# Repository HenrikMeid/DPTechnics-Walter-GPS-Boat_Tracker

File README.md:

### Lage:

Ein Sportboot wird von mehreren Parteien genutzt. Darüber hinaus ist es mit einer automatischen Lenzpumpe ausgestattet, die bei Regenfall das im Boot anfallende Wasser abpumpt. Um die aktuelle Position des Bootes für alle Beteiligten sichtbar zu machen, gefahrene Routen nachvollziehen zu können und zusätzlich zu erkennen, ob die automatische Pumpe tatsächlich aktiv war, wurde das folgende Projekt umgesetzt.  

# DPTechnics Walter Boat-tracker

Das obenstehende Projekt nutzt die [GNSS](https://de.wikipedia.org/wiki/Globales_Navigationssatellitensystem)- und LTE-Funktionalität des [DPTechnics Walter Dev Boards](https://www.quickspot.io/index.html), um Positions- und Sensordaten eines Sportbootes zu erfassen und an ein serverseitiges Backend zu übertragen. Dieses speichert die empfangenen Daten in einer Datenbank und bereitet sie in einem [Webfrontend](#Walktrough) zur Darstellung auf.
Die nachfolgende Grafik stellt den Ablauf schematisch dar.

Der DPTechnics Walter sendet seine aktuelle Position sowie beliebige weitere Sensorwerte ([GPIO's](https://de.wikipedia.org/wiki/GPIO)) per CoAP oder [HTTPS](https://de.wikipedia.org/wiki/Hypertext_Transfer_Protocol) POST an die DynDNS-Adresse des Servers, der zusätzlich durch einen Reverse Proxy ([NGINX](https://de.wikipedia.org/wiki/Nginx)) abgesichert ist. Über entsprechende Routen werden die Daten mit einem Zeitstempel versehen und in eine SQLite-Datenbank geschrieben.

Zur Verarbeitung und Darstellung der Daten auf einem Webserver kommt serverseitig ein Python-[Flask](https://flask.palletsprojects.com/en/stable/deploying/)-Skript zum Einsatz. Der gesamte Datenaustausch erfolgt aktuell über API-Calls mit dem [Flask-Server](https://flask.palletsprojects.com/en/stable/deploying/). [Gunicorn](https://gunicorn.org/) fungiert dabei als [WSGI-Server](https://de.wikipedia.org/wiki/Web_Server_Gateway_Interface) und übernimmt das Handling mehrerer User-Clients sowie die [WSGI-HTTPS](https://de.wikipedia.org/wiki/Web_Server_Gateway_Interface)-Übersetzung.

Über die Website können Anfragen – beispielsweise zur aktuellen Position des Bootes – an den Server gestellt werden. Dieser liest die entsprechenden Daten aus der Datenbank aus und übergibt sie an das JavaScript der Webseite, welches sie visuell darstellt.

Für ein zweckmäßiges [CD/CI-Setup](https://de.wikipedia.org/wiki/CI/CD) wurde für den privaten Einsatz die [GitHub Container Registry (GHCR)](https://github.blog/news-insights/product-news/introducing-github-container-registry/) gewählt. Diese kann alternativ problemlos durch den offiziellen [Docker Hub](https://www.docker.com/products/docker-hub/) ersetzt werden ([Infos zu Containerization](https://en.wikipedia.org/wiki/Containerization_(computing))). Entsprechende [Crontabs](https://de.wikipedia.org/wiki/Cron) oder [Webhooks](https://de.wikipedia.org/wiki/Webhook) sind derzeit eigenständig zu implementieren.

# Getting started

Notwendige Hardware- und Softwareanpassungen werden in den folgenden Kapiteln erläutert.

## Prerequisits

> [!NOTE]
>
> * Voraussetzung ist eine eigene global erreichbare IP oder [DynDNS-Adresse](https://de.wikipedia.org/wiki/Dynamisches_DNS). Sehr zu empfehlen ist der kostenlose DynDNS-Host [IPv64.de](https://ipv64.net/)
> * Ebenso wird ein bereits installierter Reverse Proxy o. ä. wie [NGINX](https://nginx.org/) für eine einfache [Let's-Encrypt](https://de.wikipedia.org/wiki/Let%E2%80%99s_Encrypt)-[TLS](https://de.wikipedia.org/wiki/Transport_Layer_Security)-Zertifizierung und optionales Loadbalancing benötigt.
> * Zusätzlich wird eine vorhandene Docker- bzw. Docker-Compose-Installation vorausgesetzt. Siehe [Docker Doku](https://docs.docker.com/engine/install/)
> * Für die Programmierung des ESP32 wurde die [Arduino IDE](https://docs.arduino.cc/software/ide/) verwendet. Details zur Verwendung der Development-Toolchain in der [Arduino IDE](https://docs.arduino.cc/software/ide/) befinden sich in der [DPTechnics Walter Doku](https://www.quickspot.io/documentation.html#/developer-toolchains/arduino)

## Hardware

Das folgende Kapitel erläutert die getroffenen hardwareseitigen Maßnahmen und listet die verwendeten Bauteile auf.

### ESP32 GPIOS

Um die 12 V- und 24 V-Spannungen des Bordnetzes als 3.3 V-Logiksignale nutzbar zu machen, wurde die nachstehende Schaltung entworfen und auf einer Lochrasterplatine umgesetzt.

Die Schaltung für das Erkennen der Pumpe auf der linken Seite ist rechts gespiegelt, nachfolgend wird sich auf die linke Seite beschränkt. Die beim Schalten des Verbrauchers GPIO_13 (Pumpe) anliegende Spannung (Vcc_Boradnetz, 12 -24 V) wird über C2 geglättet und durch D1 auf 10 V begrenzt. Die Spannung am Spannungsteiler R2/R3 schaltet anschließend Q1. Die am Pull-up R4 anliegende Spannung von 3.3 V wird dadurch annähernd auf GND gezogen, wodurch die GPIO's 13 und 38 einen Flankenwechsel erkennen (Wake-up, Interrupt etc.). Dabei kann der [Interrupt/Wakeup](https://de.wikipedia.org/wiki/Interrupt) an GPIO_38 über den Jumper JP1 wahlweise dazugeschalten werden, wenn dieser bei einem Flankenwechsel an GPIO_13 aktiv sein soll. Möchte eine analoge Spannung über einen der internen [ADC's](https://de.wikipedia.org/wiki/Analog-Digital-Umsetzer) gemessen werden, kann das PCB um einen niederohmigen [Trimmer](https://de.wikipedia.org/wiki/Trimmer) an GPIO_12 erweitert werden. Um im weiterer Zukunft weitere [GPIO's](https://de.wikipedia.org/wiki/GPIO) nutzbar machen zu können wurden die GPIOs 40, 41, 42, 2, 1 und 7 an Buchsenleisten herausgeführt. Ebenfalls herausgeführt sind die Seriellen GPIOs 44 und 43, werden aber nicht verwendet. Pin 26 / GPIO_0 versorgt die 3.3 V Ebene des [PCB's](https://de.wikipedia.org/wiki/Polychlorierte_Biphenyle) mit 3.3 V, sowie GND die GND Ebene des zweilagigen PCB (Siehe nächste Abbildung).

Die Pull-up-Spannung wird über den internen [DC/DC-Wandler](https://de.wikipedia.org/wiki/Gleichspannungswandler) des [ESP](https://de.wikipedia.org/wiki/ESP32) selbst bereitgestellt (GPIO_0 = LOW), sofern der [ESP](https://de.wikipedia.org/wiki/ESP32) mit 3.3–5 V über USB-C oder Walter Pin 28 versorgt wird. Da die 3.3 V / 250 mA-Spannungsquelle ebenfalls den Sequans LTE/GNSS-[SoC](https://de.wikipedia.org/wiki/System-on-a-Chip) versorgt, ist es notwendig, neben den internen [Pull-ups](https://www.elektronik-kompendium.de/public/schaerer/pullr.htm) zusätzlich einen externen zu verwenden.

Die Bauteile bzw. die Schaltung wurde nach den Bauteilen entworfen, welche bereits in der Werkstatt des Autors vorhanden waren. Es mag durchaus bessere Lösungen geben. Die [Via's](https://de.wikipedia.org/wiki/Durchkontaktierung) sind einfach da weil der Platz vorhanden ist und warum nicht, kostet nicht mehr, tut niemandem weh und mir macht's Spaß.

DPTechnics Walter / ESP Pinning siehe -> [Doku](https://www.quickspot.io/documentation.html#/hardware/walter). Anschaulich dargestellt ist die fertige Hardware in der oberen Abbildung der Assembly.

> [!IMPORTANT]
> Wichtig ist eine konstante Spannungsquelle für den ESP. Eventuelle Laderegler von Powerbanks o. ä. beenden die Spannungsversorgung im Light- oder Deep-Sleep-Modus des ESP.

### Energieverbrauch

Das System bezieht im getesteten Szenario ca. 11 mAh/Tag (1 h im Zustand/State Fahrt, 23 h deep sleep).  
Im deep sleep Modus, also im Zustand/State Hafen, wird ca. 0,25 mAh/Tag verbraucht.

### Server

Als Server eignet sich grundsätzlich jede lauffähige Hardware. Hier wurde ein Raspberry Pi 5 mit 8 GB RAM verwendet.

### Teileliste

Mindest Anzahl 1x GPIO IN + 1x GPIO Wakeup + 1x ADC-Trimmer GPIO IN:

* Reichelt
  * 1x DPTechnics Walter
  * 4x 1k Widerstand MPR 1,00K
  * 1x 10 V Zener-Diode BZX 85C10 VIS
  * 1x 1x2 Jumper BKL 10120190
  * 1x 1x2 Stiftleiste BKL 10120909
  * 2x 1x14 Buchsenleiste BKL 10120952
  * 1x 1x3 Buchsenleiste BKL 10120717
  * 1x 1x5 Buchsenleiste BKL 10120643
  * 1x Schraubklemme CTB0502-2
  * 2x Schraubklemme CTB0102-3
  * 1x Trimmer 10k 64Y-10K
  * 1x PCB oder Lochrasterplatine LR-DS-KIT
  * 1x Gehäuse 3215000,0H
* Amazon

  * 1x [8 Ader 10AWG Kabel](https://www.amazon.de/dp/B0F2J3JX1M?ref=ppx_yo2ov_dt_b_fed_asin_title)
  * 1x [USB-A DC/DC Wandler 12-5 V](https://www.amazon.de/dp/B0D471BSR2?ref=ppx_yo2ov_dt_b_fed_asin_title)
  * 1x [Schraubverbinder](https://www.amazon.de/dp/B0CYLPM7T7?ref=ppx_yo2ov_dt_b_fed_asin_title)
  * 1x [Sicherungshalter](https://www.amazon.de/dp/B00H3CVSXQ?ref=ppx_yo2ov_dt_b_fed_asin_title)
  * 1x [100 mA Sicherung](https://www.amazon.de/BOJACK-sicherungen-Sortiment-transparenten-Kunststoffbox/dp/B07TF68QZC/ref=sr_1_1_sspa?__mk_de_DE=%C3%85M%C3%85%C5%BD%C3%95%C3%91&crid=N28PGBRT44MQ&dib=eyJ2IjoiMSJ9.sPdAgH-rSnJFHYjegg6Dek2Q75fIi0S6McFGhtfZCjzgh_EctIML_GrF6OmgXMo4czIO8cW98SZEgSEyAAEJxmwuqdoz92V_l-mYqf2NKlNrb9KftnxUi-83u6B079BJfZob5SS1ncg14YnqM1RtYm1rnb2NeMVneedfPabSAqy4ZyhohT7ycUOSktVEu5QRGCjuL90_8qmFwU3k02jZVjznu-b97ms8FXkPfLcSCucvuZw9p0O4m7MyqG4ajsIcs_8uYud1AMbCneMqnoGVlf6sbl-t8s_liqoBa6SfKPQ.GSThK7u_IChCK4kmN7Saj6kUuYZNWmGNsO2dPPZifQI&dib_tag=se&keywords=sicherung%2B150%2BmA%2BF&qid=1770633179&sprefix=sicherung%2B150a%2Bf%2Caps%2C123&sr=8-1-spons&aref=S2wg4qFQ5A&sp_csd=d2lkZ2V0TmFtZT1zcF9hdGY&th=1)
* Bereits vorhanden sein sollte:

  * Altes USB-A Kabel zum verbasteln
  * Crimps etc.

## ESP32S3 Code

Damit der ESP32 die Sensorwerte an den Server senden kann, müssen folgende Parameter in der .ino bzw. den Header-Files des ESP-Codes an den entsprechenden Stellen eingetragen werden:

* IP / URL:

```
#define HTTPS_HOST "adresse.home64.de"

```

* Ports:

```
#define HTTPS_PORT 443
```

* GET / POST Endpoints: (wenn andere gewünscht)

```
#define HTTPS_GET_ENDPOINT "/daten"
#define HTTPS_POST_ENDPOINT "/daten"
```

* BasicAuth Zugangsdaten

```
#define HTTP_USER "user"
#define HTTP_PASS "userpasswort"
```

* **Einmalig** TLS CA:
  Dabei wird das [CA-Zertifikat](https://en.wikipedia.org/wiki/Certificate_authority) mit `PROGMEM` im [Flash](https://de.wikipedia.org/wiki/Flash-Speicher) des ESP32 gespeichert.

```
const char ca_cert[] PROGMEM = R"EOF(
-----BEGIN CERTIFICATE-----
/*Hier CA einfuegen*/
-----END CERTIFICATE-----
)EOF";
```

Die `.tlsWriteCredential()` Methode in `setupTLSProfile()` sollte demnach auch nur einmal nach Eintragung des [CA-Zertifikat](https://en.wikipedia.org/wiki/Certificate_authority) ausgeführt werden. Danach darf der Teil gerne auskommentiert werden (siehe Codebeispiel unten). Anschließend wird das [CA-Zertifikat](https://en.wikipedia.org/wiki/Certificate_authority) beim Setup des TLS-Profils aus dem Flash geladen.

```
bool setupTLSProfile(void){
  // Sollte nur bei Aenderung des CA certs und nach Firmwareupgrade aufgerufen werden
  /*if(!modem.tlsWriteCredential(false, 12, ca_cert)) {
    Serial.println("Error: CA cert upload failed");
    return false;
  }*/

  if(modem.tlsConfigProfile(HTTPS_TLS_PROFILE, WALTER_MODEM_TLS_VALIDATION_CA,
                            WALTER_MODEM_TLS_VERSION_13, 12)) {
    Serial.println("INFO: TLS profile configured");
  } else {
    Serial.println("ERROR: TLS profile configuration failed");
    return false;
  }

  return true;
}
```

> [!TIP]
> Welche [TLS-Version](https://ssl.de/ssl-faq/welche-tls-versionen-gibt-es.html) auf dem eigenen Server verwendet wird, kann mit [openssl](https://openssl.org/) überprüft werden:
>
> ```
> openssl s_client -connect adresse.de:0000 -tls1_2
> ```
>
> Dort einfach alle drei Versionen durchprobieren.
> Das verwendete CA lässt sich am besten über einen beispielhaften [POST](https://en.wikipedia.org/wiki/POST_(HTTP)) via [curl](https://curl.se/) im Terminal ermitteln:
>
> ```
> curl --trace-ascii debug.txt -u username:userpw -X POST https://adresse.de/end-point -d "sensor=test&wert=42"
> ```

## Python Server

Die folgenden serverseitigen Einstellungen sind in der [settings.json](https://de.wikipedia.org/wiki/JSON) vorzunehmen:

* User / Passwort:
  In der settings.json sind die Standardnutzer und Standardpasswörter zu ersetzen. Diese werden in der server.py geparsed und begrenzen über [Decorators](https://de.wikipedia.org/wiki/Decorator) den Zugriff auf die jeweiligen Routen.

```
{
    "users": {
        "admin": "adminpasswort",
        "user": "userpasswort"
    }
}
```

* Ports:
  Bei Bedarf kann der Port in der docker-compose.yml auf den Wunschport YYYY geändert werden
> [!CAUTION]
> Docker Überschreibt die internen IP Tables der [UFW](https://de.wikipedia.org/wiki/Uncomplicated_Firewall)(Firewall)! Unbedingt beim  betreiben auf einem [VPS](https://cloud.google.com/learn/what-is-a-virtual-private-server?hl=de) eine vor dem Server liegende Firewall verwenden und [Ports](https://de.wikipedia.org/wiki/Port_(Netzwerkadresse)) in der docker-compose.yml auf [local host (127.0.0.1)](https://de.wikipedia.org/wiki/Localhost) binden.  
  
```
    Ports:
    - 127.0.0.1:YYYY:5000
```

## Instalation

Durch die Docker-Kapselung gestaltet sich die Installation denkbar einfach durch Klonen des [Repos](https://de.wikipedia.org/wiki/Repository)

```
git init
git clone 
```

und Ausführen der docker-compose.yml

```
docker compose up -d
```

# Walktrough

## ESP32

Welche Werte gesendet werden sollen sowie weitere Einstellungen wie die Hafenkoordinaten erhält der ESP durch einmaliges Herunterladen der [esp_settings.json](https://de.wikipedia.org/wiki/JSON) bei jedem Neustart. Weiteres dazu im [Dashboard](#dashboard).  

### Funktion

Die State-Machine des ESP32 kennt zwei Grundzustände: Hafen und Fahrt. Nach dem Start evaluiert der ESP seinen Zustand durch Messen der aktuellen Position und Vergleich mit den hinterlegten Hafenkoordinaten (esp_settings.json).

Befindet sich der ESP im Hafen, sendet er diesen Zustand an den Server/die Website und geht anschließend für 15 Minuten in den Light-Sleep-Modus, bevor er seine Position erneut evaluiert.

Befindet sich der ESP außerhalb des Hafens, befindet er sich im Zustand Fahrt und sendet seine Position im 1-Minuten-Takt an den Server/die Website. Ob die Pumpe läuft (`GPIO_PIN_13 == HIGH`) wird dabei über Interrupts in jedem Zustand erkannt und an den Server gemeldet.

Über Modifizierung der HTTPS [POST's](https://en.wikipedia.org/wiki/POST_(HTTP)) können beliebige Werte gesendet werden. Der Server und die Datenbank übernehmen diese automatisch, sofern sie der folgenden Syntax folgen:

```
curl -u admin:adminpasswort -X POST -d "sensor=<EIGENER_WERT>>&wert=<EIGENER_WERT>" https://adresse.de:5000/daten
```

## Dashboard

Über das Dashboard werden jene Eigenschaften und Parameter festgelegt, die später vom ESP nach einem Neustart in Form der esp_setting.json übernommen werden – insbesondere die Hafenkoordinaten.

## Logs

Im Reiter "Logs" werden alle [POST's](https://en.wikipedia.org/wiki/POST_(HTTP)) des ESP dargestellt. Über das Formular können diese nach Zeitraum gefiltert werden.

## Karte

Im Reiter Karte wird die aktuelle bzw. letzte Position des ESP/Bootes dargestellt. Über das Formular oberhalb der Karte kann der Positionsverlauf (Fahrt/Trip) visualisiert und nachvollzogen werden. Das Zeitformat im Datumsformular entspricht [UTC](https://de.wikipedia.org/wiki/Koordinierte_Weltzeit), die Anzeige in der Karte UTC + Z. Durch Klicks in der Map können Bojen/Positionsmarker gesetzt werden (rein visuell und zur Positionsanzeige).\
Über die Google Maps- und Apple Maps-Buttons gelangt man zur aktuellen Position in der entsprechenden App.

# Code
Die nachfolgenden Kapitel erläutern die grobe Struktur und den Aufbau des ESP32 Codes sowie die des Python Backends.
## ESP32
Der ESP Code besteht aus einem Setup Teil und einem Cooperative Scheduler in den folgenden Files:  
berta_2p0_ESP32.ino: Hauptfile (Setup+Scheduler, main.c)  
berta.h  
berta.c: Setup- und Hilfsfunktionen  
berta_states.h  
berta_states.c: States und Hilfsfunktionen der States  

### Setup
```
setup(){
}
```
Der Setupteil (berta_2p0_ESP32.ino) beginnt mit der Konfiguration des [Watchdogs](https://de.wikipedia.org/wiki/Watchdog), welcher nur im Setup läuft, die [Statemachine](https://de.wikipedia.org/wiki/Endlicher_Automat) hat ein eigenes Fehlermanagement. Im Anschluss werden die GPIO's und Wakeups konfiguriert, welche in der Statemachine für das Aufwachen und Detektieren verantwortlich sind, wenn ein Anschalten der Pumpe erkannt wird. Zuletzt wird der [EEPROM](https://de.wikipedia.org/wiki/Electrically_Erasable_Programmable_Read-Only_Memory), GNSS, TLS und HTTPS konfigureirt. Im EEPROM werden nur die Hafenkoordinaten gespeichert und nur Überschrieben wenn neue Koordinaten im Backend vorliegen. Details zu GNNS, TLS und HTTPS sind der [DPTechnics Walter Doku](https://www.quickspot.io/documentation.html#/) zu entnehmen.

### Scheduler und State Machine
```
while(1) {
    switch (mainState){
      case REC_SETUP:       // 0
        recSetup();
        break;
        ...
    }
  }
}
```

Der die Logik zum senden der Positions und Sensordaten wurde im Rahmen eines einfachen [Cooperative Schedulers](https://en.wikipedia.org/wiki/Cooperative_multitasking) umgesetzt (berta_2p0_ESP32.ino). Dieser unterscheidet zwischen den folgenden States (mainStates):  
Die folgende Grafik (Erstellt mit KI Claude Code) verdeutlicht den Ablauf. Die Pfeile zeigen etwas durch die Gegend aber wenn man sich an Der Farbe und der Richtung orientiert passt alles.  

```
enum MainStates { 
    REC_SETUP, // 0
    SETTING_UP, // 1
    EVAL_STATE, // 2
    HAFEN, // 3
    FAHRT, // 4
    ERROR, // 5
    SLEEP_STATE, // 6
    SWITCH_PRESSED // 7
};
```
 
Im Setupteil wird der mainState zunächst auf REC_SETUP gesetzt.  
**REC_SETUP**: In diesem State wird die esp_settings.json vom Server geladen, in welcher sich zur Zeit nur die Hafenkoordinaten befinden und welche ebenfalls über das Dashboard im Webinterface bearbeitet werden kann.  
**SETTING_UP**: Vergleicht ob die im EEPROM hinterlegten Hafenkoordinaten denen in der JSON entsprechen und überschreibt diese, falls geändert.  
**EVAL_STATE**: Zunächst wird der Zustand der GPIOs überprüft, ist die Pumpe aktiv, wird in den Zustand SWITCH_PRESSED gewechstelt. Danach fordert wird ein GNSS Fix angefordert und Vergleichen ob der erhaltene Fix innerhalb der Hafenkoordinaten liegt oder nicht. Da nicht detektiert werden kann ob der Motor läuft oder nicht, wird hierüber bestimmt ob sich das Boot im Hafen befindet oder außerhalb, in Fahrt. Befindet sich das Boot im Hafen wird in den Zustand Hafen gewechselt. Befindet sich das Boot außerhalb der Hafenkoordinaten wird in den Zustand Fahrt gewechselt.  
**HAFEN**: Der ESP sendet den Zustand Hafen ans Backend und welchselt in den Zustand SLEEP_STATE.  
**FAHRT**: Der ESP sendet die aktuelle Position ans Backend. Befindet sich das Boot weiterhin außerhalb des Hafens, wird eine Minute gewartet und wieder in EVAL_STATE gewchselt.  
**ERROR**: Wird in irgendeiner Funktion als Rückagbewert `false` detektiert, beispielsweise beim Verbindungsaufbau mittels LTE, wird automatisch in den Zustand ERROR gewechselt. Wurde während der Laufzeit 5 mal in den Zustand ERROR gewechselt, führt der ESP beim 5. Wechsel in den ERROR Zustand einen Softwarereset durch.  
**SLEEP_STATE**: Der Wakeuppin wird konfiguriert, sodass dieser den ESP bei Aktivierung wieder aus dem Sleepmode aufwecken kann (Pump wird während sleep aktiv). Im Anschluss wird für 15 Minuten in den light sleep des ESP gewechselt. Nach dem Aufwachen (nach 15 min. oder wakeup) wird der Wakeuppin deaktiviert und in den Zustand EVAL_STATE gewechselt.  
**SWITCH_PRESSED**: Wurde die Pumpe aktiviert (0 V zu 12 V an `SWITCH_PIN`) wird dieser Zustand als `pumpe = True` ans Backend gesendet, ebenso wenn der Wechsel von 12 V an 0 V statt findet, dann eben `pumpe = False`. Anschließend wird wieder in EVAL_STATE gewechselt (nur Flankenwechsel werden ans Backendgesendet, Pumpe an/aus).  

## Backend
Das Backend verfolgt die folgende Ordnerstruktur:  
- app
    - data
        - sensor_data.db
    - logs
        - app.log
    - static
        - dashboard
            - dashboard.js
        - index
            - index.js
        - karte
            - karte.js
        - logos.png
    - templates
        - base.html
        - dashboard.html
        - index.html
        - karte.html
    - esp_settings.json
    - settings.json
    - requirements.txt
    - server.py
    - bertaSetup.py
    - routes.py
- figures
    - figures.png
- befehle.txt
- docker-compose.yml
- Dockerfile
- README.md
  
 Über das Dockerfile und docker-compose.yml kann das Projekt selbst gebaut werden, wenn man nicht auf die Github Container Registry zurückgreifen will. Dazu befinden sich in der requirements.txt alle notwendigen Abhängigkeiten. In der befehle.txt befinden sich allerlei Befehle die sich im Verlauf des Projektes als hilfreich herausgestellt haben. Der Webserver wird bei Verwendung von Docker hinter Gunicorn laufen, kann aber auch als virtual environment unter Python laufen. Das Hauptfile ist hier die server.py. Über die bertaSetup.py werden die Zugangsdaten (Anmeldedaten) auf der Weboberfläche geladen und die Hilfsfunktionen initialisiert. Wurde in der server.py die Datenbank in /data erstellt und der Server gestartet, werden die Routen über die routes.py geladen. In der routes.py befinden sich auch die API Routen, welche bei Bedarf auch als externe api.py ausgelagert werden können. Die Webseiten werden aus den entsprechenden HTML Files in /templates erstellt, welche auf das JavaSrcipt in /static zurückgreifen, worin sich ebenfalls alle Logos und Grafiken befinden. Alle [Serverlogs](https://de.wikipedia.org/wiki/Logdatei) werden eigentlich an die Dockerausgabe weitergereicht, hier werden diese ebenfalls in ein eigenes Logfile in /logs geschrieben.

# Sonstiges

* Die Dokumentation zum Walter DevBoard befindet sich nochmals [hier](https://www.quickspot.io/documentation.html#/), samt dem Datenblatt [hier](https://www.quickspot.io/datasheet/walter_datasheet.pdf).
* Als Inspiration für den ESP32-Code dienten die DPTechnics Examples by [@Arnoud Devoogdt](arnoud@dptechnics.com).
* Die Icons in der Website stammen von [flaticon.com](https://www.flaticon.com/).
* Die OpenSeamap-Integration wurde durch [Leaflet](https://leafletjs.com/) ermöglicht.

# Upcomming
Weitere geplante Features:  
* Roaming: Über die Weboberfläche soll Roaming an und ausgeschaltet werden.  
* CoAP: Aktuell läuft alle Kommunikation über HTTPS. Das ist aktuell praktisch um nicht extra einen CoAP Server betreiben zu müsen
und Website sowie Walter können über Routen implementiert werden. Auch Text, Zahlen und vor allem der Austausch von json ist 
einfacher zu implementieren. Zukünftig soll aber die Kommunikation durch CoAP ergänzt werden.  
* Postgres: SQL wurde einzig verwendet um mir grundlegende Datenbankkenntnisse anzueignen. soll um Postgress erweitert werden und das Setup so verschlankt werden.  
* Online Reset: Über die Weboberfläche soll ein Reset des Trackers anfragbar sein um einen Neustart und somit ein Update der esp_settings.json zu erzwingen.  
* OTA: Die Software soll zukünftig OTA aktualisiert werden können.

### Addition v1.1
---
- Eine Tabelle unter der Karte zeigt listet nun die 5 letzten erkannten Ausfahrten des Boots auf. Durch anklicken einer Zeile wird der Trip
  in der Karte direkt dargestellt, ohne manuell mit der Datumseingabe danach suchen zu müssen. Ein Trip beginnt mit der letzten Hafenkoordinate
  nach verlassen des Hafens und endet mit der ersten Hafenkoordinate nach Einfahren in den Hafen. Sollen weiter zurück liegende Ausfahrten in
  der Tabelle gelistet werden, Trägt man den gewünschten Zeitraum im Datums Formular über der Karte ein und bekommt alle Trips in diesem
  Zeitraum angezeigt.

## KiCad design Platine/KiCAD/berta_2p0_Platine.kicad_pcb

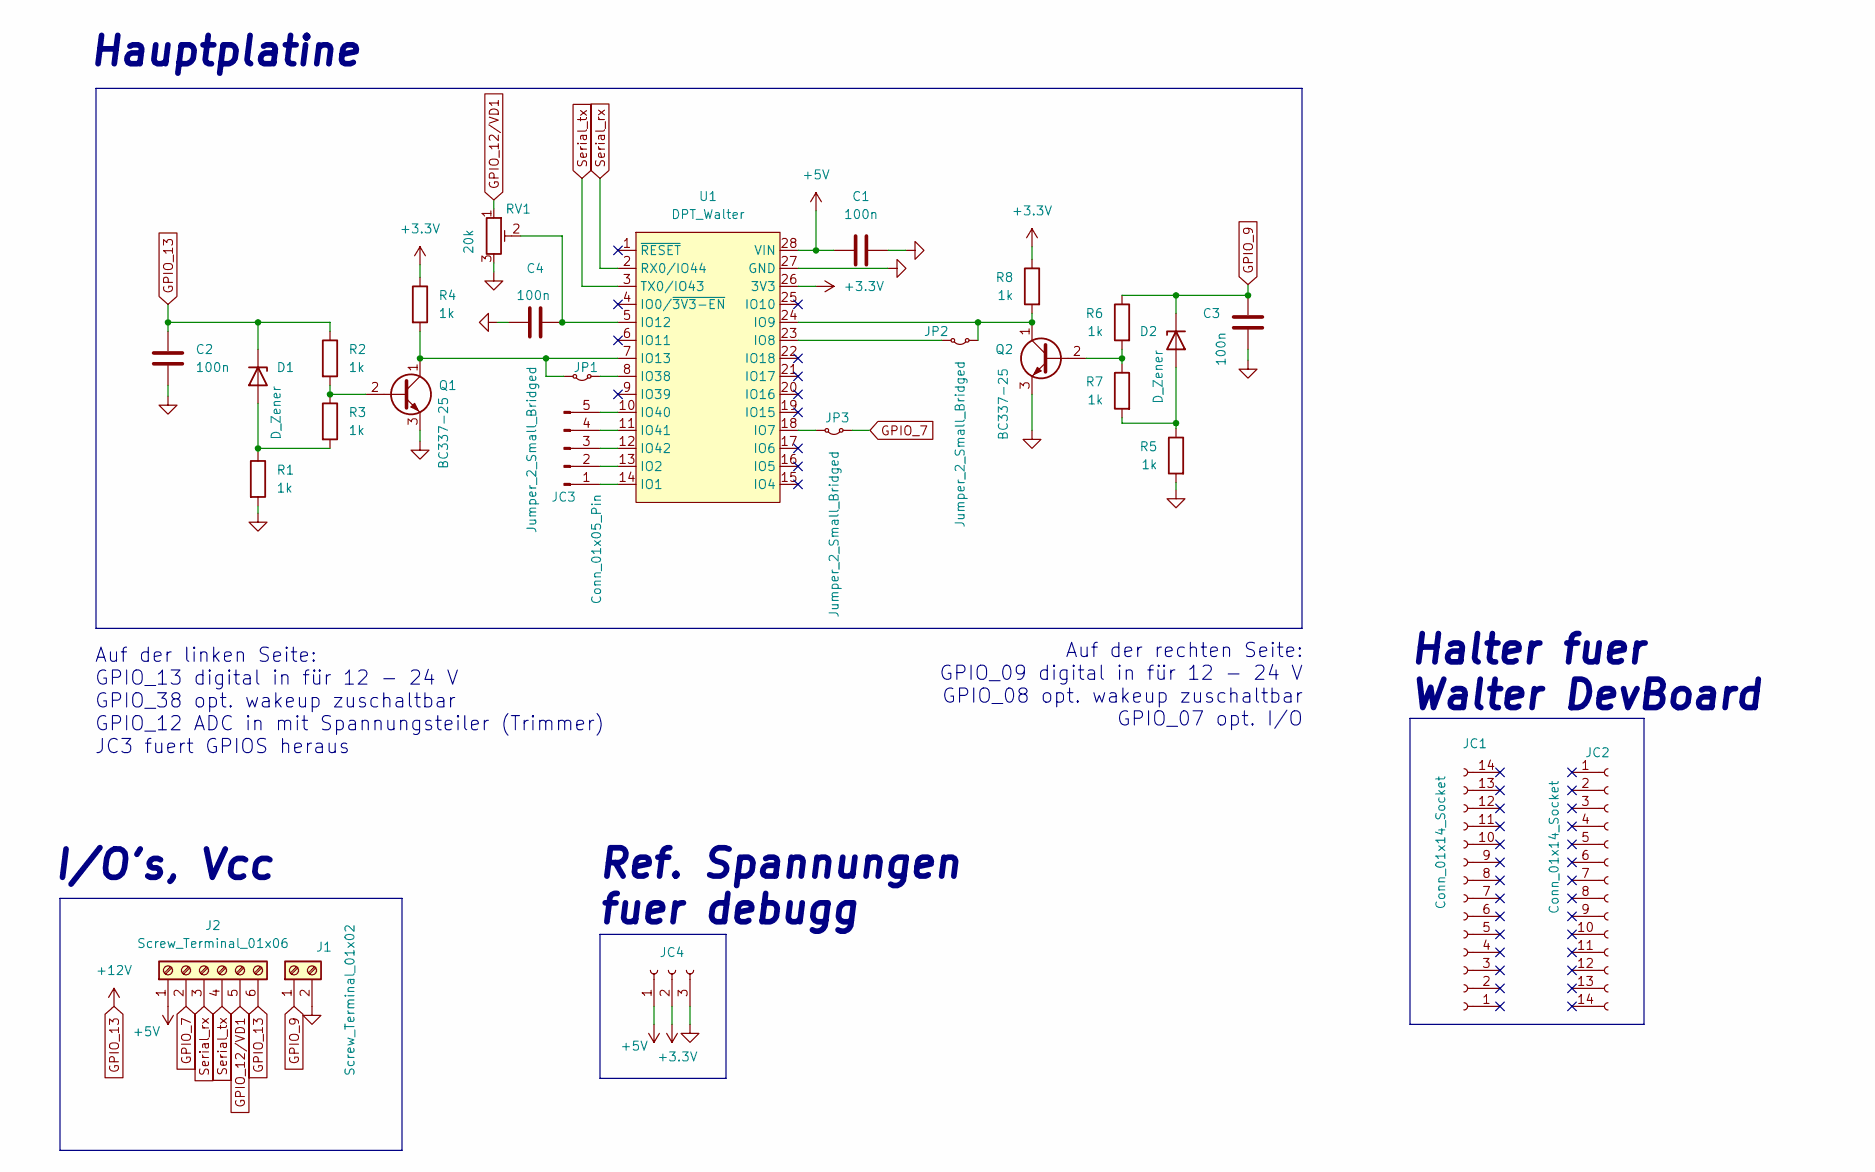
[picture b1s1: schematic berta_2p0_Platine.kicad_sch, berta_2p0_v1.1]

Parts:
C1, C2, C3, C4: 100n; C_Disc_D4.7mm_W2.5mm_P5.00mm
D1, D2: D_Zener; D_A-405_P10.16mm_Horizontal
J1: Screw_Terminal_01x02; TerminalBlock_Phoenix_MKDS-1,5-2_1x02_P5.00mm_Horizontal
J2: Screw_Terminal_01x06; TerminalBlock_Phoenix_MKDS-1,5-6_1x06_P5.00mm_Horizontal
JC1, JC2: Conn_01x14_Socket; PinSocket_1x14_P2.54mm_Vertical
JC3: Conn_01x05_Pin; PinHeader_1x05_P2.54mm_Vertical
JC4: Conn_01x03_Socket; PinSocket_1x03_P2.54mm_Vertical
JP1, JP2: Jumper_2_Small_Bridged; PinHeader_1x02_P2.54mm_Vertical
JP3: Jumper_2_Small_Bridged; SolderJumper-3_P1.3mm_Bridged2Bar12_Pad1.0x1.5mm
Q1, Q2: BC337-25; TO-92L_Wide
R1, R2, R3, R4, R5, R6, R7, R8: 1k; R_Axial_DIN0207_L6.3mm_D2.5mm_P7.62mm_Horizontal
RV1: 20k; Potentiometer_Runtron_RM-063_Horizontal
U1: DPT_Walter; walter-socket

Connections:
+3.3V: JC4.2, R4.1, R8.1, U1.26 (3V3)
+5V: C1.2, J2.1, JC4.1, U1.28 (VIN)
GND: C1.1, C2.2, C3.2, C4.2, J1.2, JC4.3, Q1.3 (E), Q2.3 (E), R1.2, R5.2, RV1.3, U1.27 (GND)
GPIO_7: J2.2, JP3.2 (B)
GPIO_9: C3.1, D2.1 (K), J1.1, R6.1
GPIO_12/VD1: J2.5, RV1.1
GPIO_13: C2.1, D1.1 (K), J2.6, R2.1
unnamed: D1.2 (A), R1.1, R3.2
unnamed: D2.2 (A), R5.1, R7.2
unnamed: JC3.1, U1.14 (IO1)
unnamed: JC3.2, U1.13 (IO2)
unnamed: JC3.3, U1.12 (IO42)
unnamed: JC3.4, U1.11 (IO41)
unnamed: JC3.5, U1.10 (IO40)
unnamed: JP1.1 (A), U1.8 (IO38)
unnamed: JP1.2 (B), Q1.1 (C), R4.2, U1.7 (IO13)
unnamed: JP2.1 (A), U1.23 (IO8)
unnamed: JP2.2 (B), Q2.1 (C), R8.2, U1.24 (IO9)
unnamed: JP3.1 (A), U1.18 (IO7)
unnamed: Q1.2 (B), R2.2, R3.1
unnamed: Q2.2 (B), R6.2, R7.1
unnamed: C4.1, RV1.2, U1.5 (IO12)
Serial_rx: J2.3, U1.2 (RX0/IO44)
Serial_tx: J2.4, U1.3 (TX0/IO43)

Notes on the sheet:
I/O's, Vcc
Halter fuer Walter DevBoard
Hauptplatine
Ref. Spannungen fuer debugg
Auf der rechten Seite: GPIO_09 digital in für 12 - 24 V GPIO_08 opt. wakeup zuschaltbar GPIO_07 opt. I/O
Auf der linken Seite: GPIO_13 digital in für 12 - 24 V GPIO_38 opt. wakeup zuschaltbar GPIO_12 ADC in mit Spannungsteiler (Trimmer) JC3 fuert GPIOS heraus

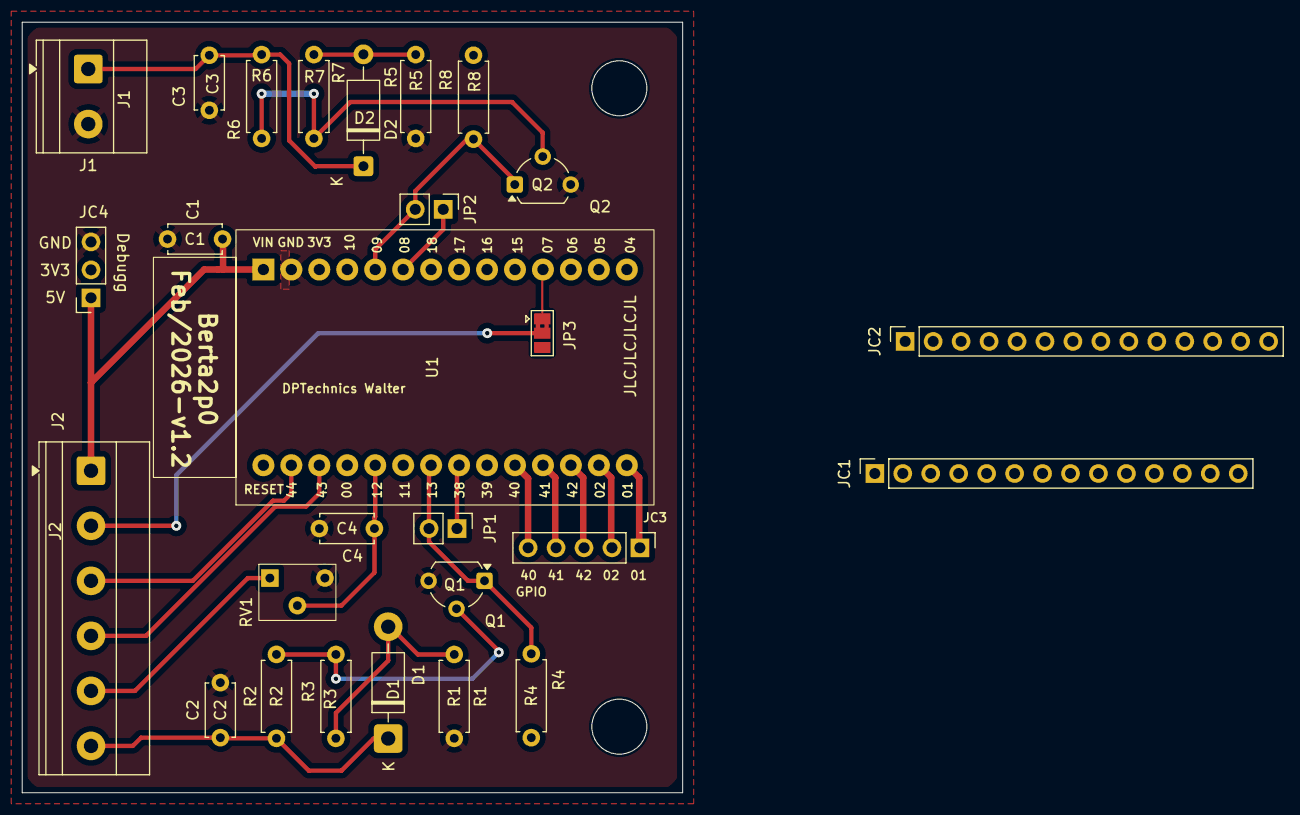
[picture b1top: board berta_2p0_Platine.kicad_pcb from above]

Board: 2 copper layers, 60.0 x 70.0 mm, 27 parts (0 on the bottom side), 24 nets.

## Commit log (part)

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2026-06-26 Batman
2026-06-26 work
2026-06-28 README.md aktualisieren
